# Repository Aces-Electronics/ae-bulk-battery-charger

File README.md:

# ae-bulk-battery-charger
large format multi-LiPo charger

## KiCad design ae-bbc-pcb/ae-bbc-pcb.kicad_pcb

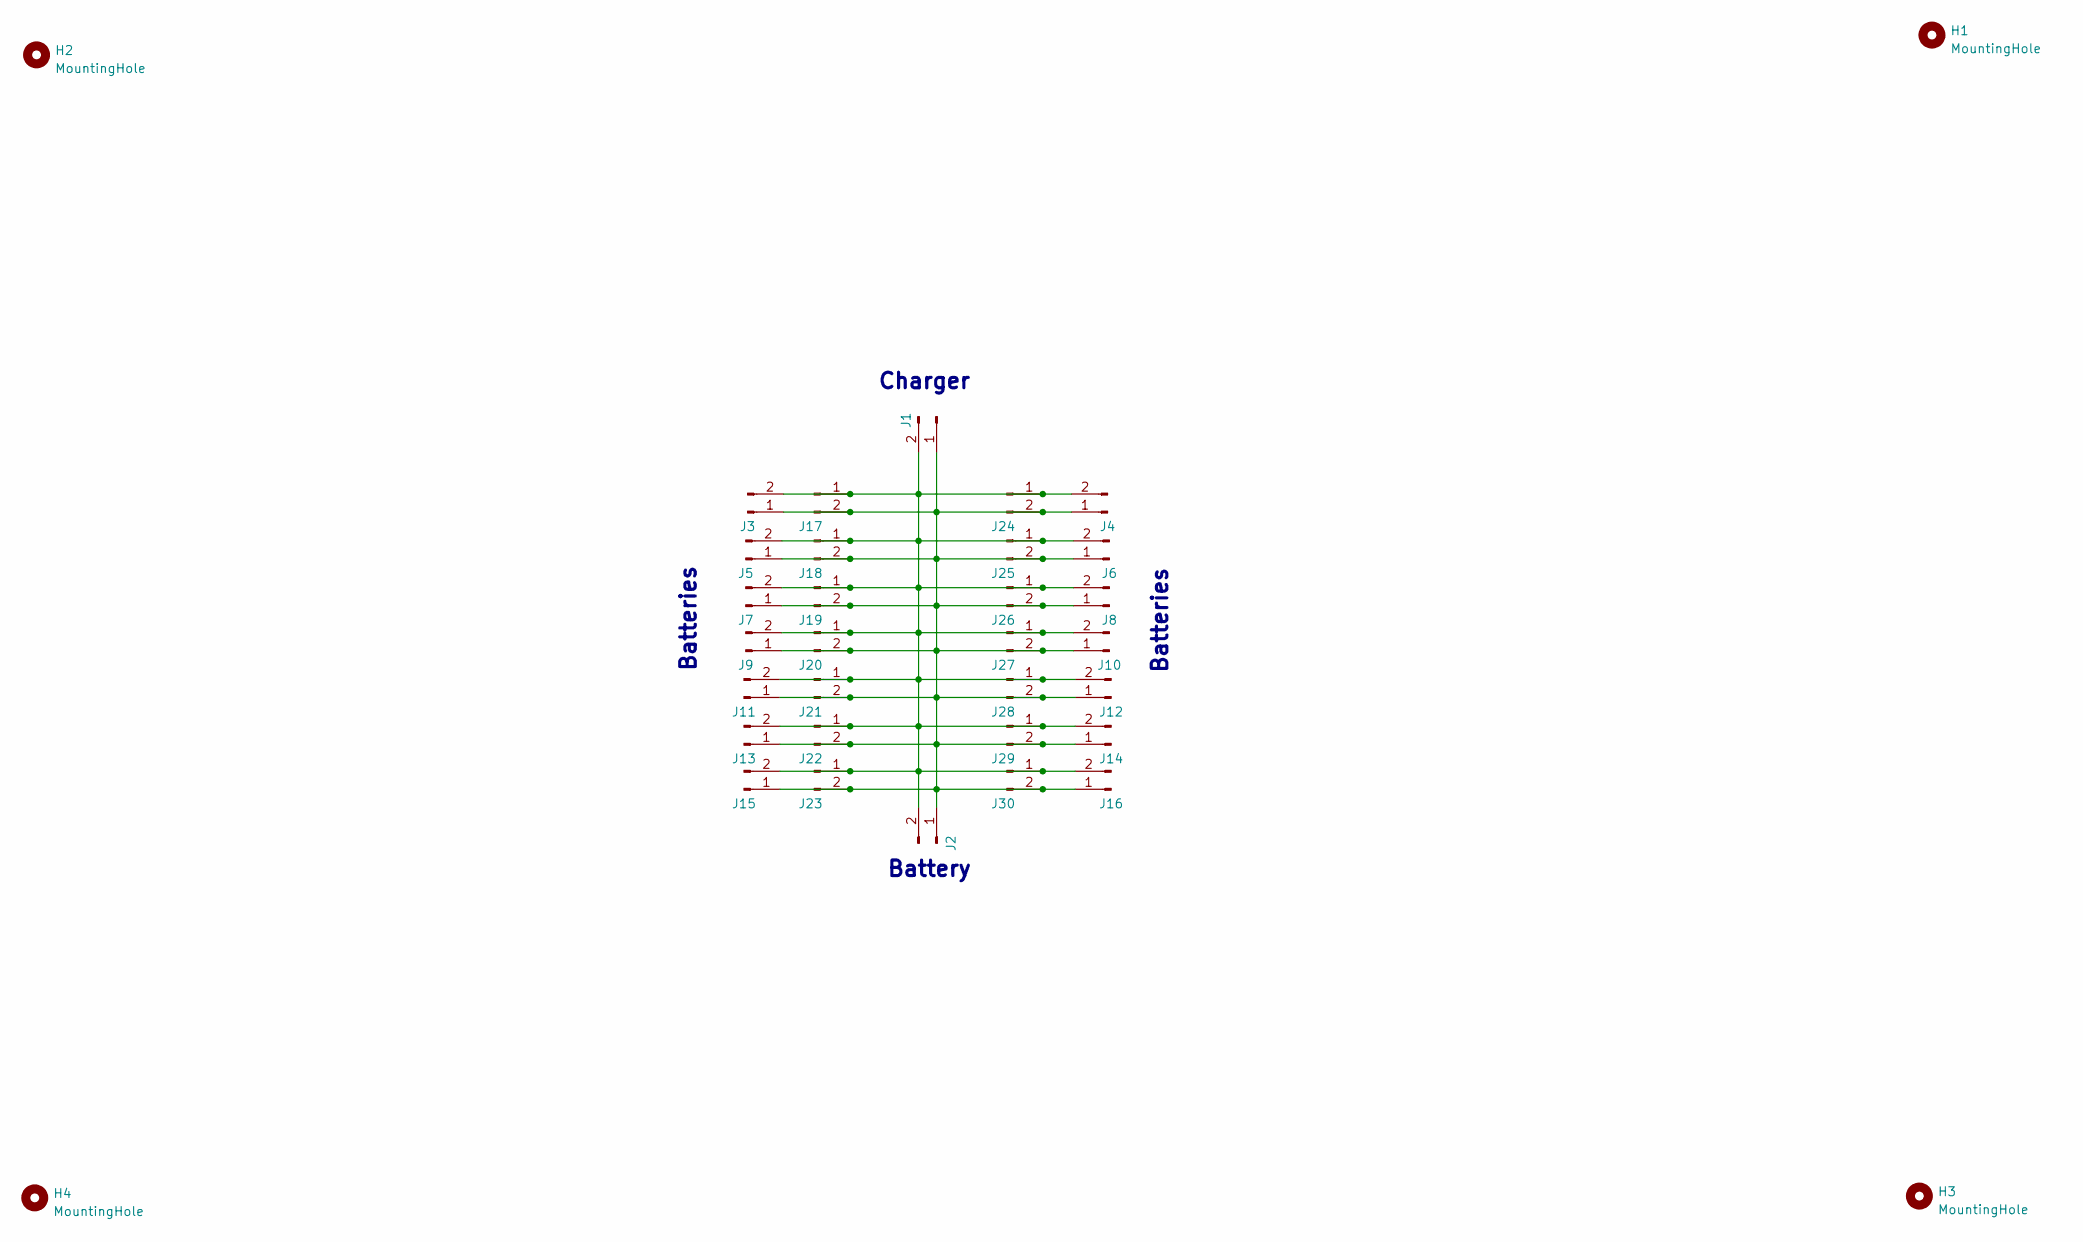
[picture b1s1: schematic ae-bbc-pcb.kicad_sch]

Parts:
H1, H2, H3, H4: MountingHole; MountingHole_3.2mm_M3_DIN965_Pad
J1: Conn_01x02_Pin; AMASS_XT60PW-F_1x02_P7.20mm_Horizontal; lcsc C428722
J2, J3, J4, J5, J6, J7, J8, J9, J10, J11, J12, J13, J14, J15, J16: Conn_01x02_Pin; AMASS_XT30PW-M_1x02_P2.50mm_Horizontal; lcsc C431092
J17, J18, J19, J20, J21, J22, J23, J24, J25, J26, J27, J28, J29, J30: Conn_01x02_Pin; JST_XH_B2B-XH-A_1x02_P2.50mm_Vertical; lcsc C158014

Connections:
unnamed: J1.1, J2.1, J3.1, J4.1, J5.1, J6.1, J7.1, J8.1, J9.1, J10.1, J11.1, J12.1, J13.1, J14.1, J15.1, J16.1, J17.2, J18.2, J19.2, J20.2, J21.2, J22.2, J23.2, J24.2, J25.2, J26.2, J27.2, J28.2, J29.2, J30.2
unnamed: J1.2, J2.2, J3.2, J4.2, J5.2, J6.2, J7.2, J8.2, J9.2, J10.2, J11.2, J12.2, J13.2, J14.2, J15.2, J16.2, J17.1, J18.1, J19.1, J20.1, J21.1, J22.1, J23.1, J24.1, J25.1, J26.1, J27.1, J28.1, J29.1, J30.1

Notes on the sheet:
Battery
Charger
Batteries

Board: 2 copper layers, 34 parts (0 on the bottom side), 2 nets, no tracks yet.

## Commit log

2024-09-04 adding files
2024-09-06 REV 0.1 to JLCPCB
2024-10-20 v0.2 waiting for feedback
